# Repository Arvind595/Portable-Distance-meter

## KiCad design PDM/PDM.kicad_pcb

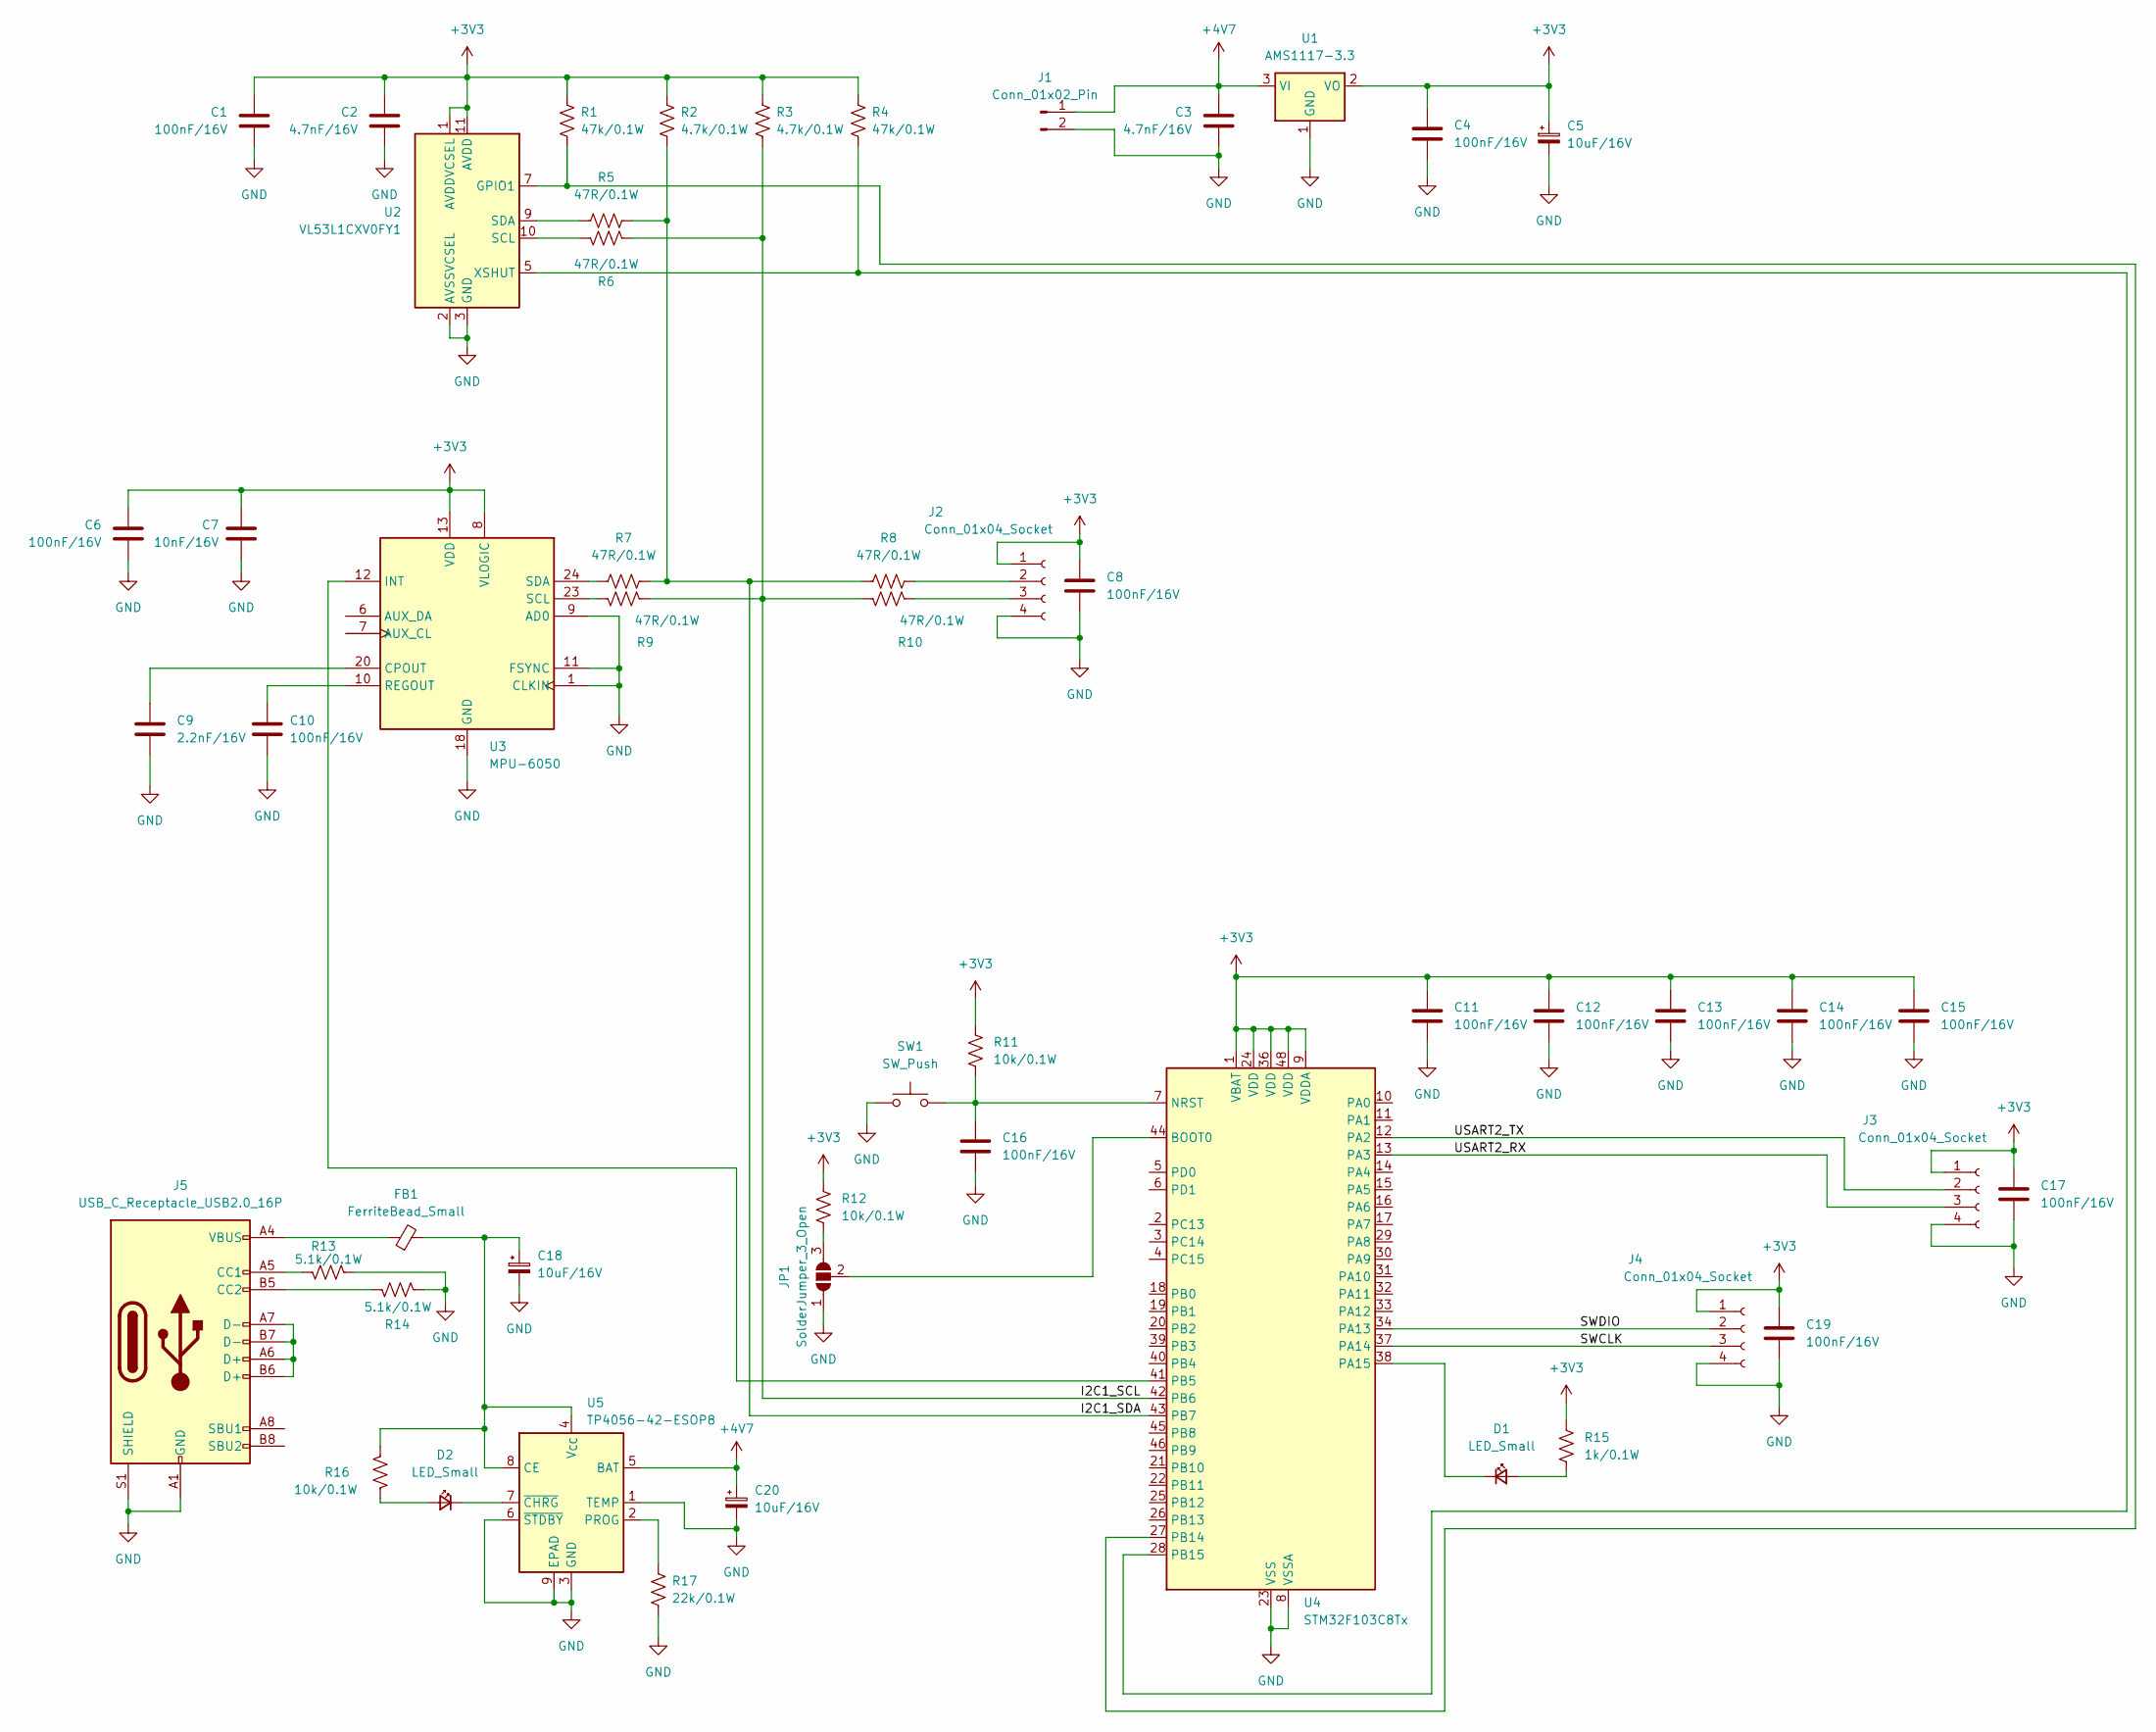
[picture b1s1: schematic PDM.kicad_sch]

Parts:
C1, C4, C6, C8, C10, C11, C12, C13, C14, C15, C16, C17, C19: 100nF/16V; C_0603_1608Metric_Pad1.08x0.95mm_HandSolder
C2, C3: 4.7nF/16V; C_0603_1608Metric_Pad1.08x0.95mm_HandSolder
C5, C18, C20: 10uF/16V; C_0805_2012Metric_Pad1.18x1.45mm_HandSolder
C7: 10nF/16V; C_0603_1608Metric_Pad1.08x0.95mm_HandSolder
C9: 2.2nF/16V; C_0603_1608Metric_Pad1.08x0.95mm_HandSolder
D1, D2: LED_Small; LED_0805_2012Metric_Pad1.15x1.40mm_HandSolder
FB1: FerriteBead_Small; L_0805_2012Metric_Pad1.15x1.40mm_HandSolder
J1: Conn_01x02_Pin; JST_EH_S2B-EH_1x02_P2.50mm_Horizontal
J2, J3, J4: Conn_01x04_Socket; PinSocket_1x04_P2.54mm_Vertical
J5: USB_C_Receptacle_USB2.0_16P; USB_C_Receptacle_XKB_U262-16XN-4BVC11
JP1: SolderJumper_3_Open; SolderJumper-3_P1.3mm_Open_Pad1.0x1.5mm_NumberLabels
R1, R4: 47k/0.1W; R_0201_0603Metric_Pad0.64x0.40mm_HandSolder
R2, R3: 4.7k/0.1W; R_0201_0603Metric_Pad0.64x0.40mm_HandSolder
R5, R6, R7, R8, R9, R10: 47R/0.1W; R_0201_0603Metric_Pad0.64x0.40mm_HandSolder
R11, R12, R16: 10k/0.1W; R_0201_0603Metric_Pad0.64x0.40mm_HandSolder
R13, R14: 5.1k/0.1W; R_0201_0603Metric_Pad0.64x0.40mm_HandSolder
R15: 1k/0.1W; R_0201_0603Metric_Pad0.64x0.40mm_HandSolder
R17: 22k/0.1W; R_0201_0603Metric_Pad0.64x0.40mm_HandSolder
SW1: SW_Push; SW_MEC_5GSH9
U1: AMS1117-3.3; SOT-223-3_TabPin2
U2: VL53L1CXV0FY1; ST_VL53L1x
U3: MPU-6050; InvenSense_QFN-24_4x4mm_P0.5mm
U4: STM32F103C8Tx; LQFP-48_7x7mm_P0.5mm
U5: TP4056-42-ESOP8; SOIC-8-1EP_3.9x4.9mm_P1.27mm_EP2.41x3.3mm_ThermalVias

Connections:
+3V3: C1.1, C2.1, C4.1, C5.1, C6.1, C7.1, C8.1, C11.1, C12.1, C13.1, C14.1, C15.1, C17.1, C19.1, J2.1, J3.1, J4.1, R1.1, R2.1, R3.1, R4.1, R11.1, R12.1, R15.1, U1.2 (VO), U2.1 (AVDDVCSEL), U2.11 (AVDD), U3.8 (VLOGIC), U3.13 (VDD), U4.1 (VBAT), U4.9 (VDDA), U4.24 (VDD), U4.36 (VDD), U4.48 (VDD)
+4V7: C3.1, C20.1, J1.1, U1.3 (VI), U5.5 (BAT)
/I2C1_SCL: R3.2, R6.2, R9.2, R10.1, U4.42 (PB6)
/I2C1_SDA: R2.2, R5.2, R7.2, R8.1, U4.43 (PB7)
/SWCLK: J4.3, U4.37 (PA14)
/SWDIO: J4.2, U4.34 (PA13)
/USART2_RX: J3.3, U4.13 (PA3)
/USART2_TX: J3.2, U4.12 (PA2)
GND: C1.2, C2.2, C3.2, C4.2, C5.2, C6.2, C7.2, C8.2, C9.2, C10.2, C11.2, C12.2, C13.2, C14.2, C15.2, C16.2, C17.2, C18.2, C19.2, C20.2, J1.2, J2.4, J3.4, J4.4, J5.A1 (GND), J5.A12 (GND), J5.B1 (GND), J5.B12 (GND), J5.S1 (SHIELD), JP1.1 (A), R13.1, R14.1, R17.2, SW1.1, U1.1 (GND), U2.2 (AVSSVCSEL), U2.3 (GND), U2.4 (GND), U2.6 (GND), U2.12 (GND), U3.1 (CLKIN), U3.9 (AD0), U3.11 (FSYNC), U3.18 (GND), U4.8 (VSSA), U4.23 (VSS), U4.35 (VSS), U4.47 (VSS), U5.1 (TEMP), U5.3 (GND), U5.6 (~STDBY), U5.9 (EPAD)
unnamed: D1.2 (A), R15.2
unnamed: D1.1 (K), U4.38 (PA15)
unnamed: D2.2 (A), R16.2
unnamed: D2.1 (K), U5.7 (~CHRG)
unnamed: FB1.1, J5.A4 (VBUS), J5.A9 (VBUS), J5.B4 (VBUS), J5.B9 (VBUS)
unnamed: J2.2, R8.2
unnamed: J2.3, R10.2
unnamed: J5.A5 (CC1), R13.2
unnamed: J5.B5 (CC2), R14.2
unnamed: J5.A6 (D+), J5.A7 (D-), J5.B6 (D+), J5.B7 (D-)
unnamed: JP1.3 (B), R12.2
unnamed: JP1.2 (C), U4.44 (BOOT0)
unnamed: R1.2, U2.7 (GPIO1), U4.27 (PB14)
unnamed: R6.1, U2.10 (SCL)
unnamed: R5.1, U2.9 (SDA)
unnamed: R4.2, U2.5 (XSHUT), U4.28 (PB15)
unnamed: C9.1, U3.20 (CPOUT)
unnamed: U3.12 (INT), U4.41 (PB5)
unnamed: C10.1, U3.10 (REGOUT)
unnamed: R9.1, U3.23 (SCL)
unnamed: R7.1, U3.24 (SDA)
unnamed: C16.1, R11.2, SW1.2, U4.7 (NRST)
unnamed: C18.1, FB1.2, R16.1, U5.4 (V_{CC}), U5.8 (CE)
unnamed: R17.1, U5.2 (PROG)

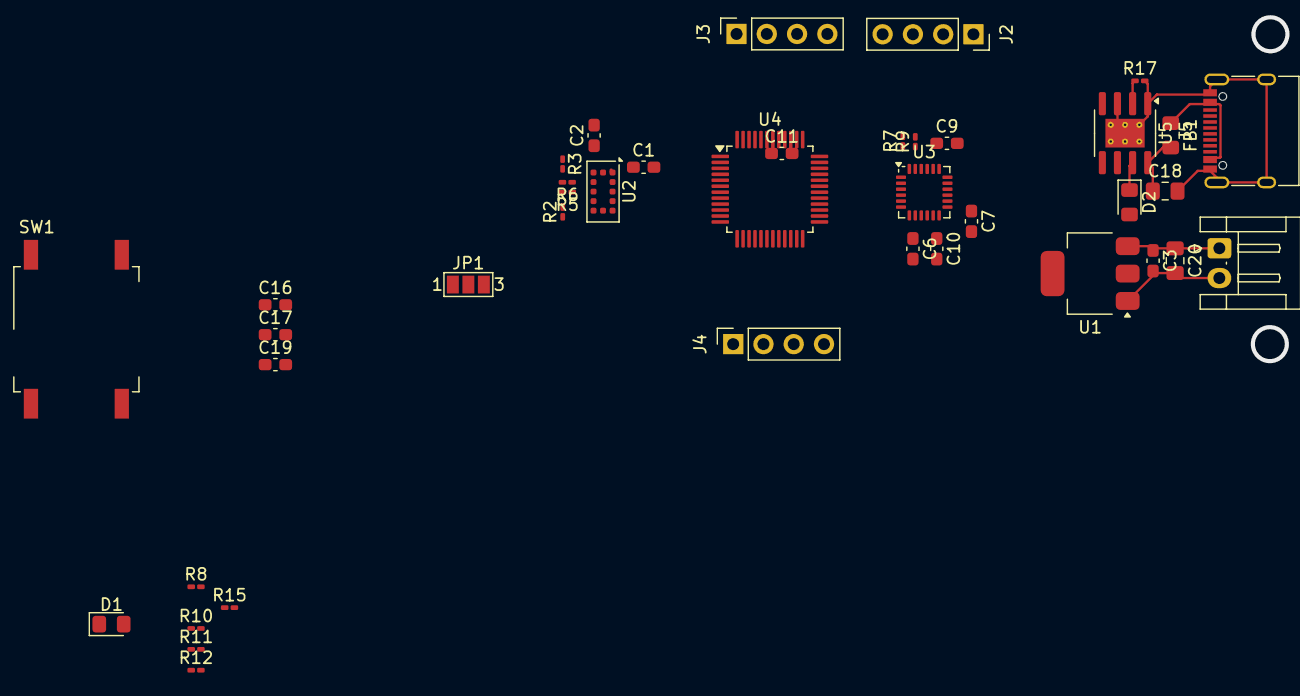
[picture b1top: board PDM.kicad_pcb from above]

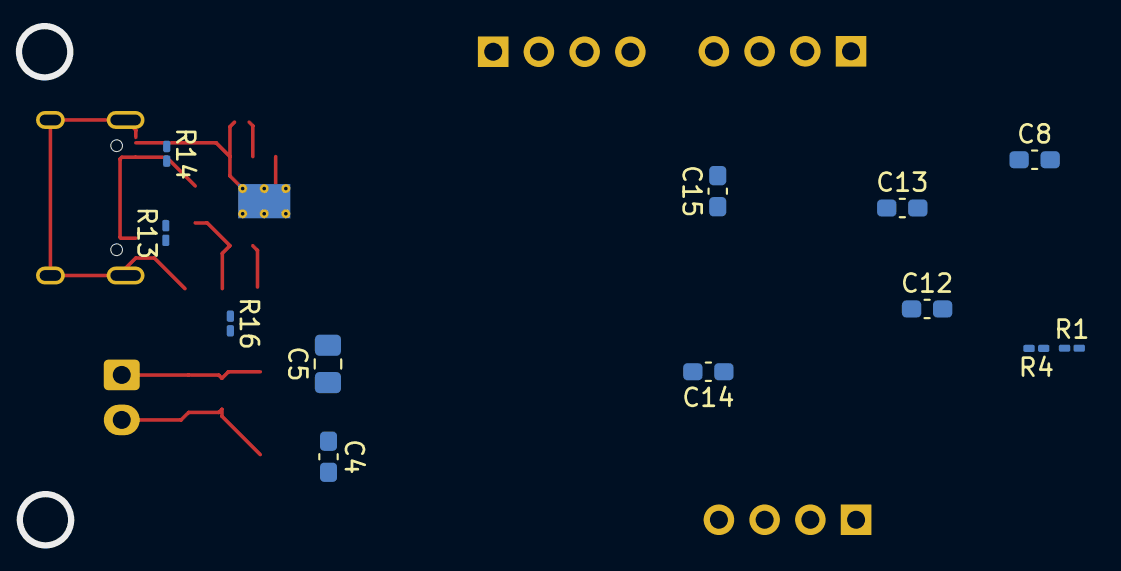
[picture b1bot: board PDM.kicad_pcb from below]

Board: 4 copper layers, 52 parts (12 on the bottom side), 33 nets.

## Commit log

2026-03-28 initial;
